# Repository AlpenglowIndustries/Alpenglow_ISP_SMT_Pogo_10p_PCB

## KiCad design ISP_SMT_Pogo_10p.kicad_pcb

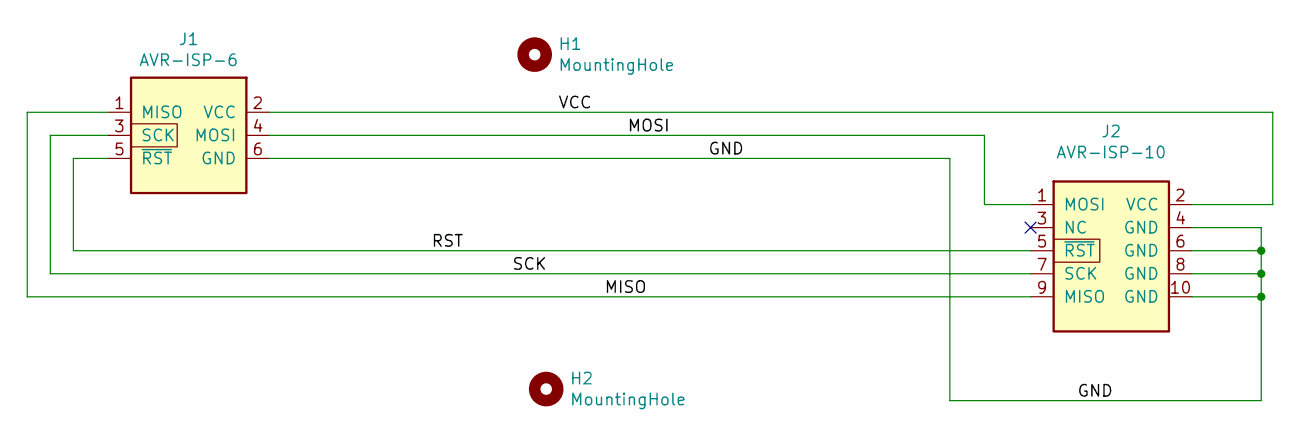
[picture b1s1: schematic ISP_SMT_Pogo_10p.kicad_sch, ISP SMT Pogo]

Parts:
H1, H2: MountingHole; MNTG-HOLE-440
J1: AVR-ISP-6; CONN-ISP-Pogo
J2: AVR-ISP-10; IDC-Header_2x05_P2.54mm_Vertical

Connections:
/GND: H1.1, H2.1, J1.6 (GND), J2.4 (GND), J2.6 (GND), J2.8 (GND), J2.10 (GND)
/MISO: J1.1 (MISO), J2.9 (MISO)
/MOSI: J1.4 (MOSI), J2.1 (MOSI)
/RST: J1.5 (~RST), J2.5 (~RST)
/SCK: J1.3 (SCK), J2.7 (SCK)
/VCC: J1.2 (VCC), J2.2 (VCC)

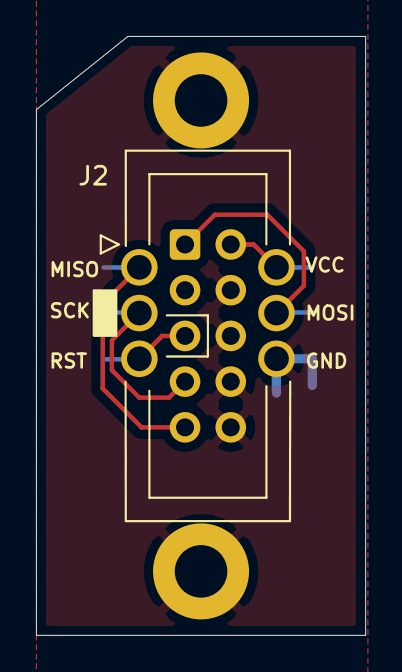
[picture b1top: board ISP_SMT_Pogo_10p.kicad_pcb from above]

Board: 2 copper layers, 18.3 x 33.3 mm, 4 parts (0 on the bottom side), 6 nets.

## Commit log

2021-11-02 renamed files
2022-10-24 Full initial commit
2022-10-26 Moved gerbers to folder, schamtic, BOM
2022-10-27 new BOM
2022-10-27 Updated gitignore, changed BOM to CSV file
